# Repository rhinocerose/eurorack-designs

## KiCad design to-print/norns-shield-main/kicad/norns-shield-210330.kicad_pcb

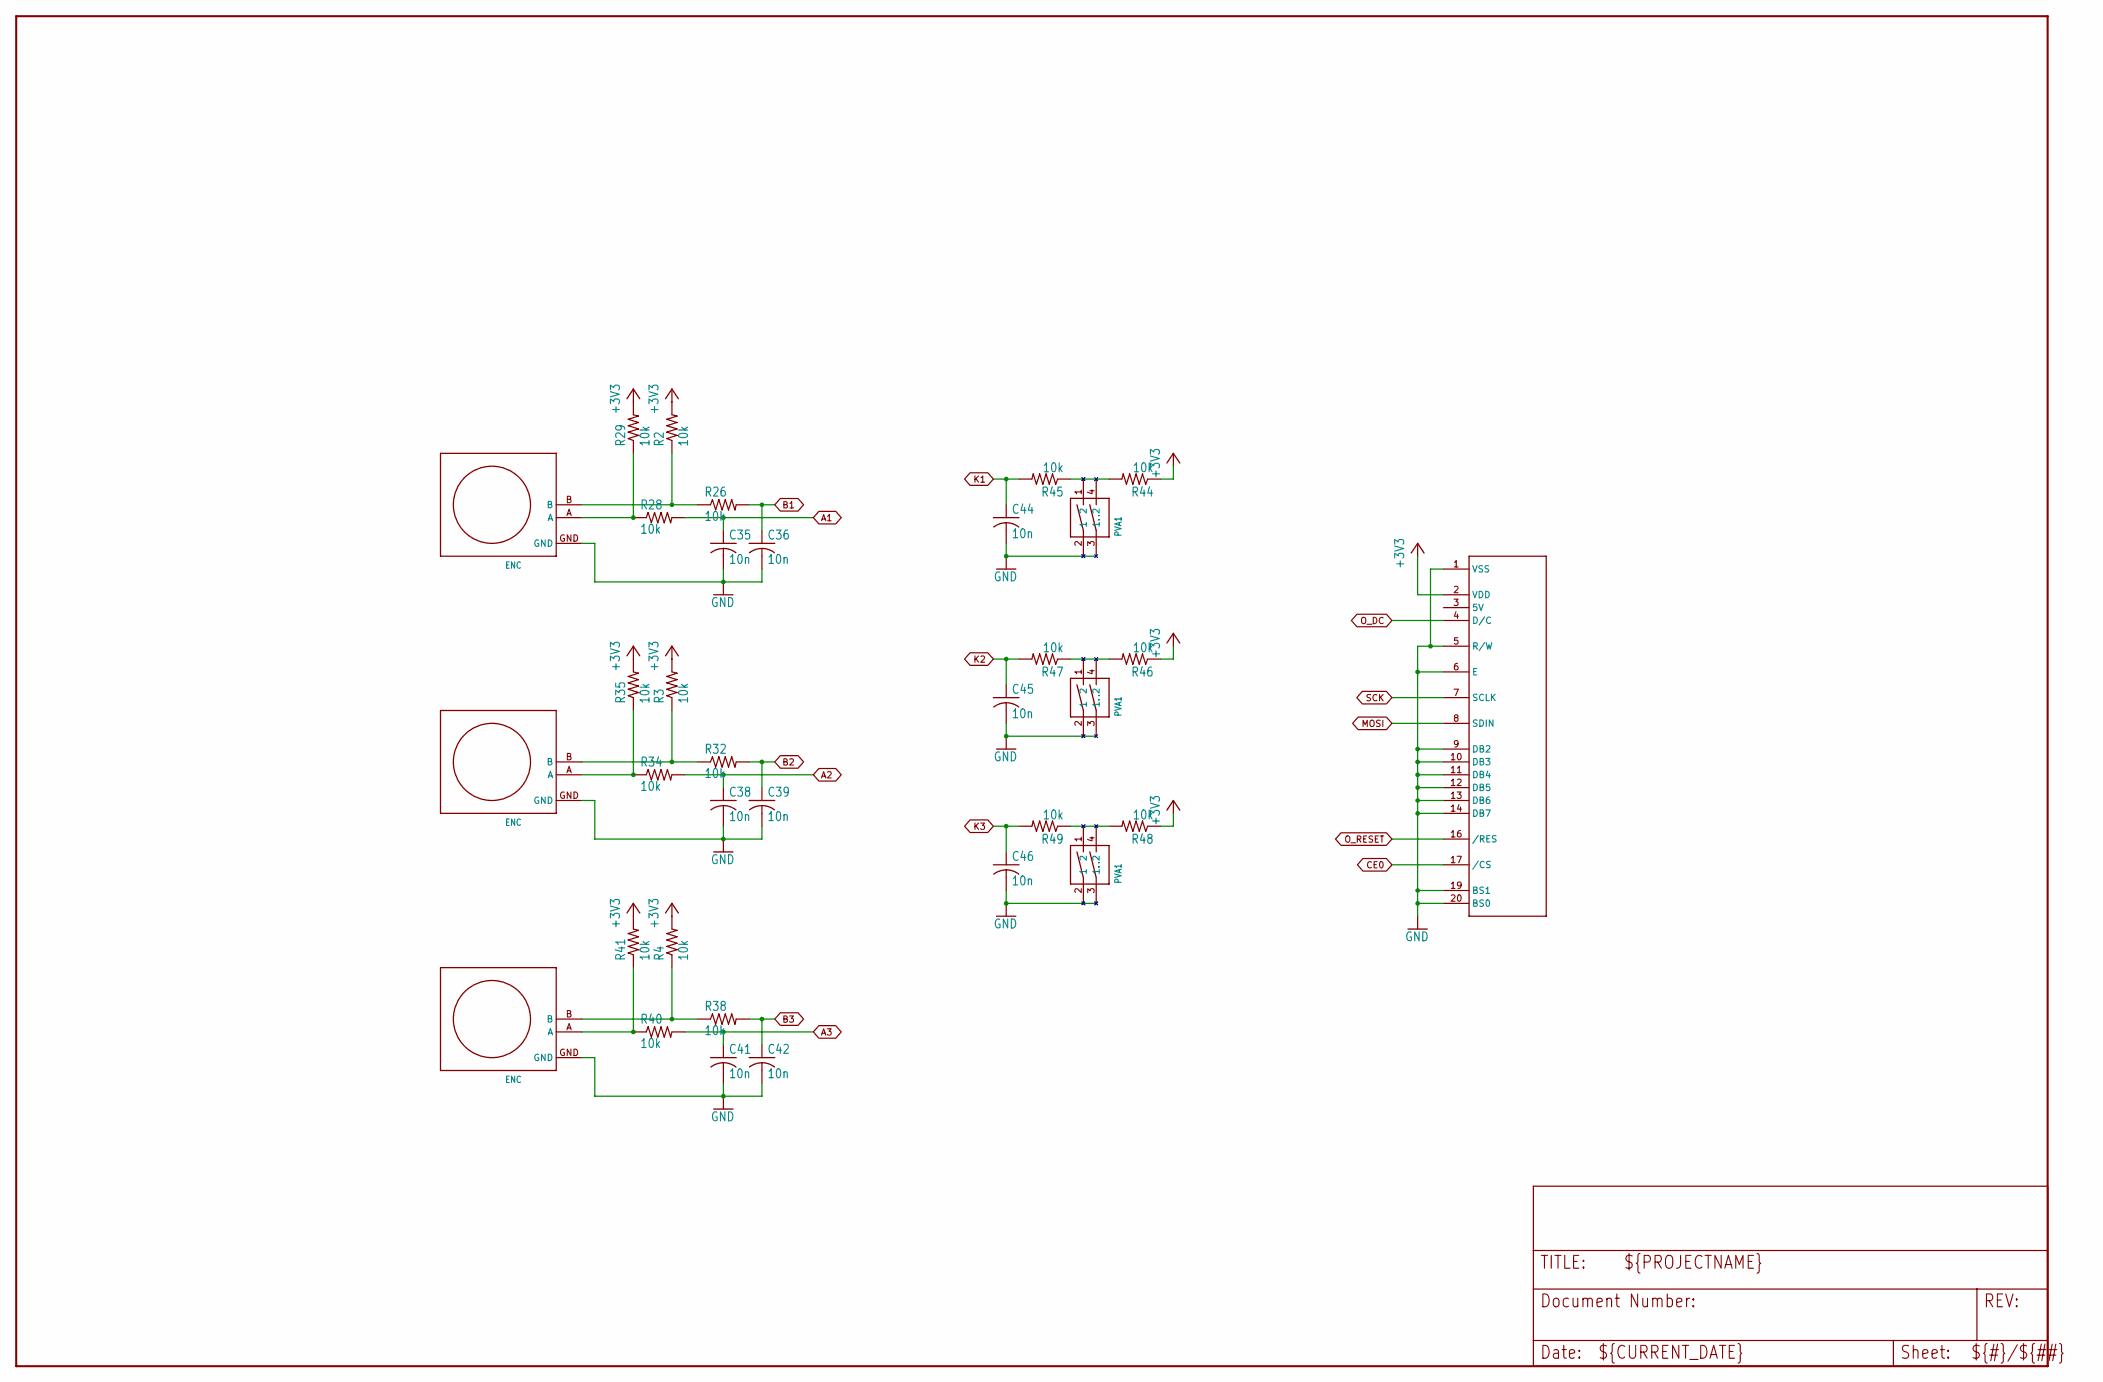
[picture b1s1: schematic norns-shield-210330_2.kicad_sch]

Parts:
C35, C36, C38, C39, C41, C42, C44, C45, C46: 10n; C0603
E1, E2, E3: ENC; PEC11RN
R2, R3, R4, R26, R28, R29, R32, R34, R35, R38, R40, R41, R44, R45, R46, R47, R48, R49: 10k; R0603
SW1, SW2, SW3: PVA1
U$1: OLED128X64; OLED-ALEPH

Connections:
+3V3: R2.2, R3.2, R4.2, R29.2, R35.2, R41.2, R44.1, R46.1, R48.1, U$1.2 (VDD); also elsewhere on the board
A1: C35.1, R28.2; also elsewhere on the board
A2: C38.1, R34.2; also elsewhere on the board
A3: C41.1, R40.2; also elsewhere on the board
B1: C36.1, R26.2; also elsewhere on the board
B2: C39.1, R32.2; also elsewhere on the board
B3: C42.1, R38.2; also elsewhere on the board
CE0: U$1.17 (/CS); also elsewhere on the board
GND: C35.2, C36.2, C38.2, C39.2, C41.2, C42.2, C44.2, C45.2, C46.2, E1.GND, E2.GND, E3.GND, SW1.2 (1), SW1.3 (1.), SW2.2 (1), SW2.3 (1.), SW3.2 (1), SW3.3 (1.), U$1.1 (VSS), U$1.5 (R/W), U$1.6 (E), U$1.9 (DB2), U$1.10 (DB3), U$1.11 (DB4), U$1.12 (DB5), U$1.13 (DB6), U$1.14 (DB7), U$1.19 (BS1), U$1.20 (BS0); also elsewhere on the board
K1: C44.1, R45.2; also elsewhere on the board
K2: C45.1, R47.2; also elsewhere on the board
K3: C46.1, R49.2; also elsewhere on the board
MOSI: U$1.8 (SDIN); also elsewhere on the board
unnamed: E1.A, R28.1, R29.1
unnamed: E1.B, R2.1, R26.1
unnamed: E2.B, R3.1, R32.1
unnamed: E2.A, R34.1, R35.1
unnamed: E3.B, R4.1, R38.1
unnamed: E3.A, R40.1, R41.1
O_DC: U$1.4 (D/C); also elsewhere on the board
O_RESET: U$1.16 (/RES); also elsewhere on the board
SCK: U$1.7 (SCLK); also elsewhere on the board

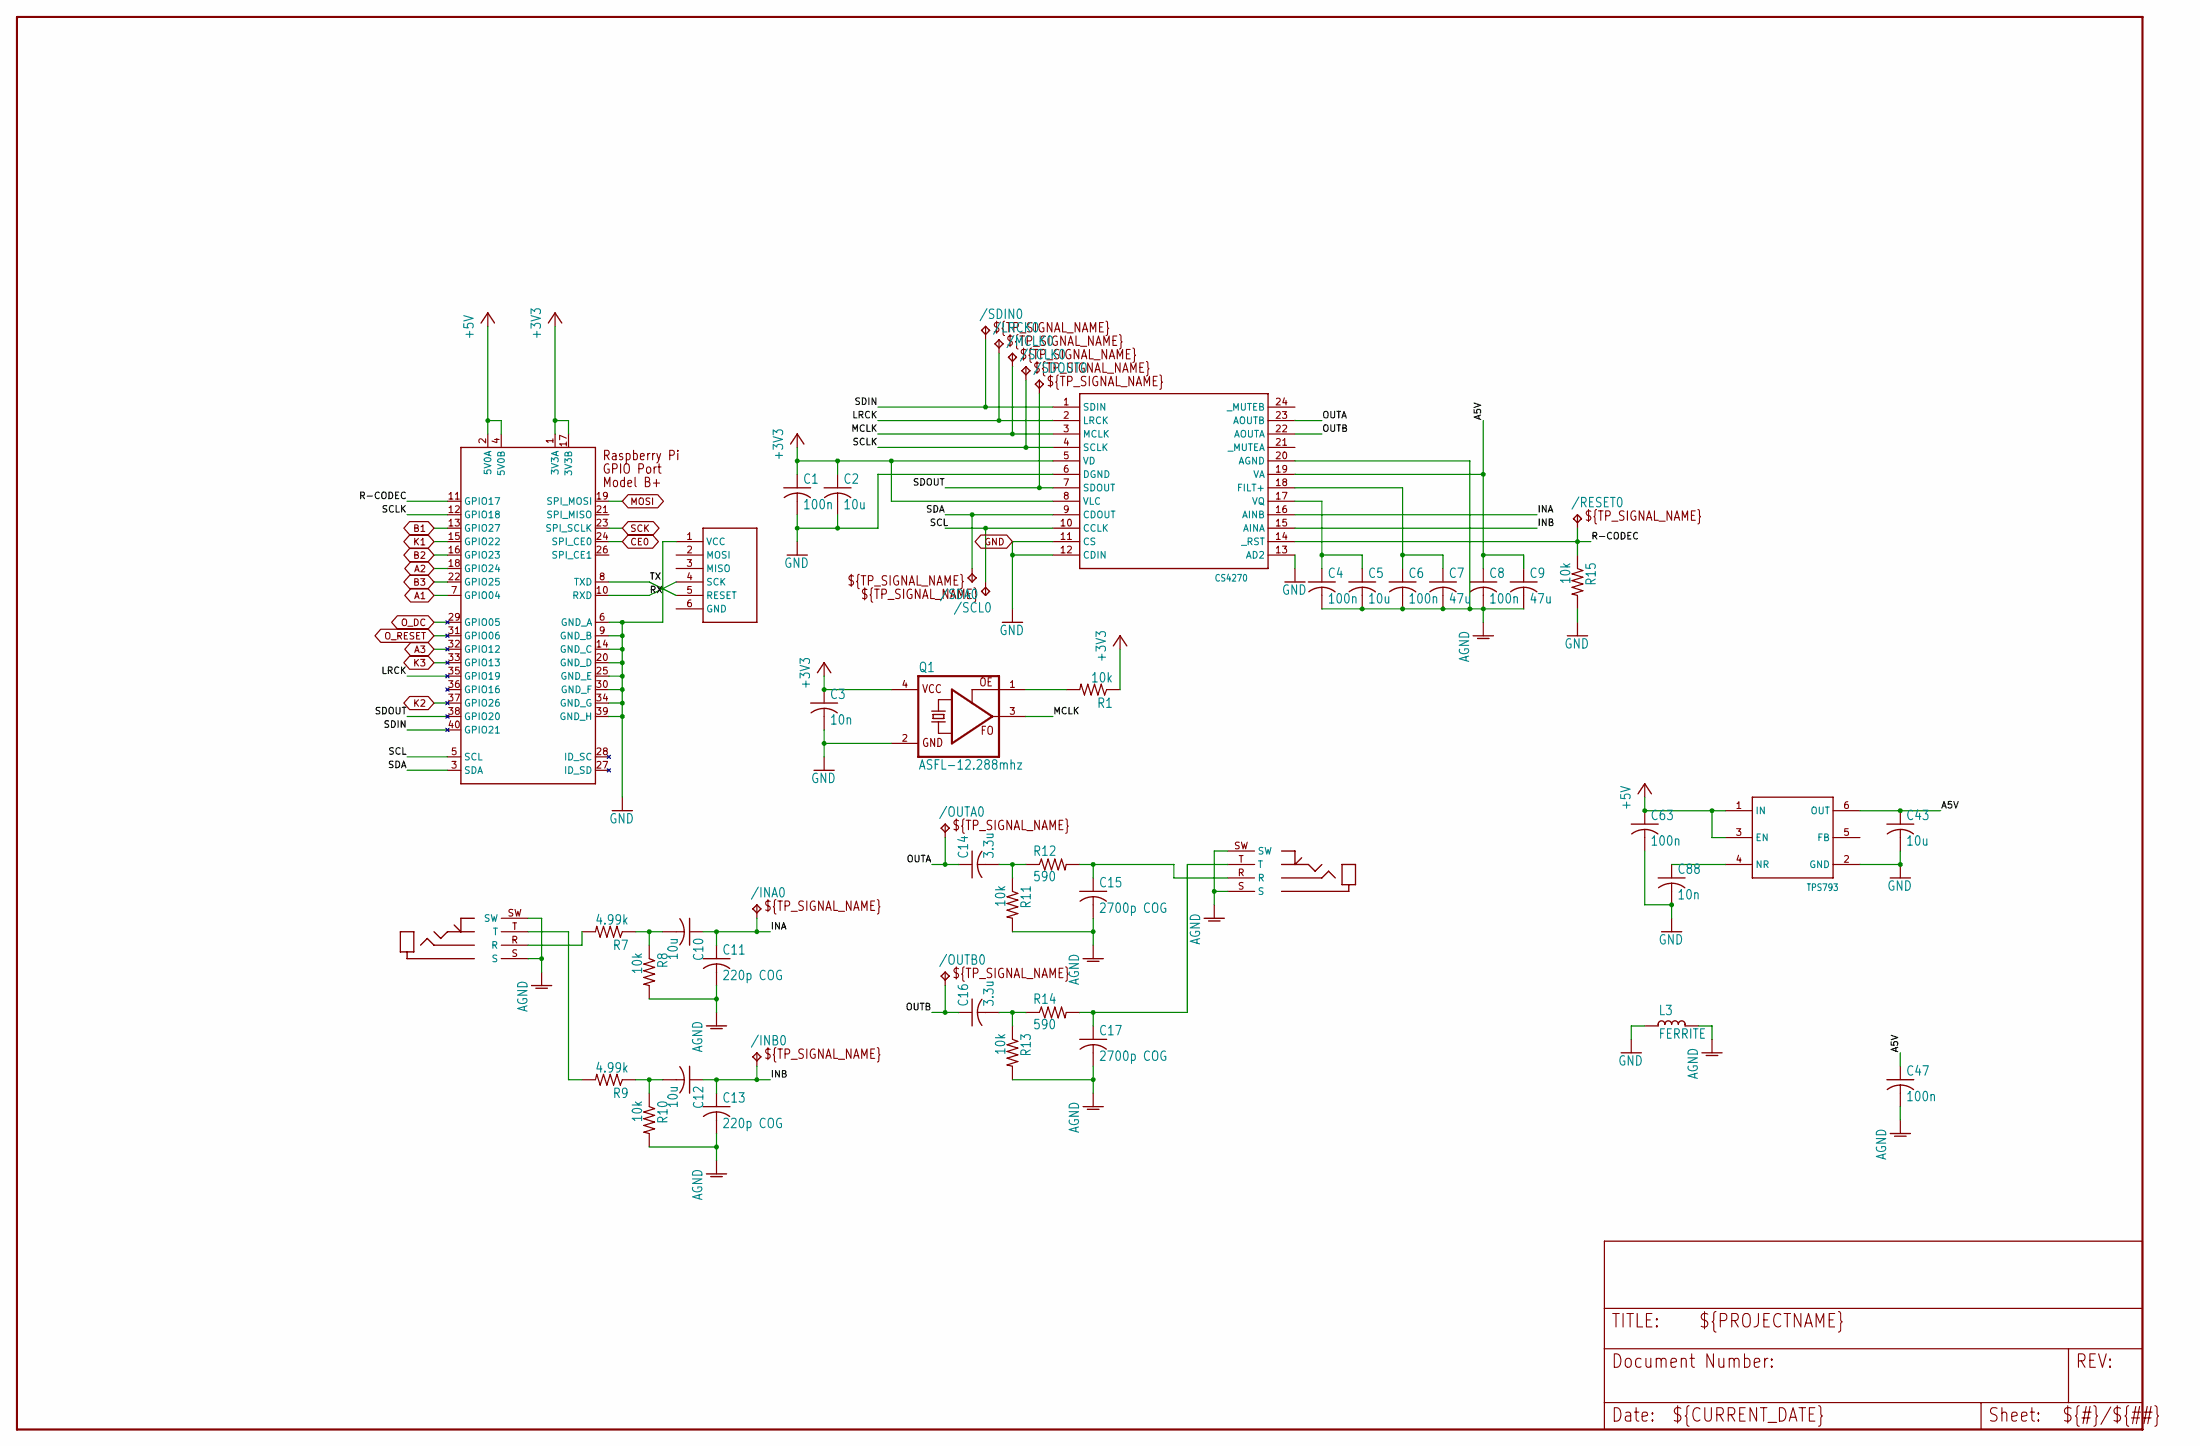
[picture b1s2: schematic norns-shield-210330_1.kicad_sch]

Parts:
/INA0: TPTP12R; TP12R
/INB0: TPTP12R; TP12R
/LRCK0: TPTP12R; TP12R
/MCLK0: TPTP12R; TP12R
/OUTA0: TPTP12R; TP12R
/OUTB0: TPTP12R; TP12R
/RESET0: TPTP12R; TP12R
/SCL0: TPTP12R; TP12R
/SCLK0: TPTP12R; TP12R
/SDA0: TPTP12R; TP12R
/SDIN0: TPTP12R; TP12R
/SDOUT0: TPTP12R; TP12R
C1, C4, C6, C8, C47, C63: 100n; C0603
C2, C5, C10, C12, C43: 10u; C0805
C3, C88: 10n; C0603
C7, C9: 47u; C1206
C11, C13: 220p COG; C0603
C14, C16: 3.3u; C0805
C15, C17: 2700p COG; C0603
J3: ISP-ROW
J-IN0: JACK-TRS-SW; JACK4832.2330
J-OUT0: JACK-TRS-SW; JACK4832.2330
L3: FERRITE; L0805
Q1: ASFL-12.288mhz; ASF
R1, R8, R10, R11, R13, R15: 10k; R0603
R7, R9: 4.99k; R0603
R12, R14: 590; R0603
U1: CS4270; TSSOP24
U11: TPS793; SSOP6
X1: RASPI_BOARD_B+#_E3; RASPI_BOARD_B+_EDGES_3DRILL

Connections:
+3V3: C1.1, C2.1, C3.1, Q1.4 (VCC), R1.1, U1.5 (VD), U1.8 (VLC), X1.1 (3V3A), X1.17 (3V3B); also elsewhere on the board
+5V: C63.1, U11.1 (IN), U11.3 (EN), X1.2 (5V0A), X1.4 (5V0B)
A1: X1.7 (GPIO04); also elsewhere on the board
A2: X1.18 (GPIO24); also elsewhere on the board
A3: X1.32 (GPIO12); also elsewhere on the board
A5V: C8.1, C9.1, C43.1, C47.1, U1.19 (VA), U11.6 (OUT)
AGND: C4.2, C5.2, C6.2, C7.2, C8.2, C9.2, C11.2, C13.2, C15.2, C17.2, C47.2, J-IN0.S, J-IN0.SW, J-OUT0.S, J-OUT0.SW, L3.1, R8.2, R10.2, R11.2, R13.2, U1.20 (AGND)
B1: X1.13 (GPIO27); also elsewhere on the board
B2: X1.16 (GPIO23); also elsewhere on the board
B3: X1.22 (GPIO25); also elsewhere on the board
CE0: X1.24 (SPI_CE0); also elsewhere on the board
GND: C1.2, C2.2, C3.2, C43.2, C63.2, C88.2, J3.1 (VCC), L3.2, Q1.2 (GND), R15.2, U1.6 (DGND), U1.11 (CS), U1.12 (CDIN), U1.13 (AD2), U11.2 (GND), X1.6 (GND_A), X1.9 (GND_B), X1.14 (GND_C), X1.20 (GND_D), X1.25 (GND_E), X1.30 (GND_F), X1.34 (GND_G), X1.39 (GND_H); also elsewhere on the board
INA: /INA0.TP, C10.1, C11.1, U1.16 (AINB)
INB: /INB0.TP, C12.1, C13.1, U1.15 (AINA)
K1: X1.15 (GPIO22); also elsewhere on the board
K2: X1.37 (GPIO26); also elsewhere on the board
K3: X1.33 (GPIO13); also elsewhere on the board
LRCK: /LRCK0.TP, U1.2 (LRCK), X1.35 (GPIO19)
MCLK: /MCLK0.TP, Q1.3 (FO), U1.3 (MCLK)
MOSI: X1.19 (SPI_MOSI); also elsewhere on the board
unnamed: Q1.1 (OE), R1.2
unnamed: C4.1, C5.1, U1.17 (VQ)
unnamed: C6.1, C7.1, U1.18 (FILT+)
unnamed: J-IN0.R, R7.2
unnamed: C10.2, R7.1, R8.1
unnamed: C12.2, R9.1, R10.1
unnamed: J-IN0.T, R9.2
unnamed: C16.2, R13.1, R14.1
unnamed: C14.2, R11.1, R12.1
unnamed: C15.1, J-OUT0.R, R12.2
unnamed: C17.1, J-OUT0.T, R14.2
unnamed: C88.1, U11.4 (NR)
OUTA: /OUTA0.TP, C14.1, U1.23 (AOUTB)
OUTB: /OUTB0.TP, C16.1, U1.22 (AOUTA)
O_DC: X1.29 (GPIO05); also elsewhere on the board
O_RESET: X1.31 (GPIO06); also elsewhere on the board
R-CODEC: /RESET0.TP, R15.1, U1.14 (_RST), X1.11 (GPIO17)
RX: J3.4 (SCK), X1.10 (RXD)
SCK: X1.23 (SPI_SCLK); also elsewhere on the board
SCL: /SCL0.TP, U1.10 (CCLK), X1.5 (SCL)
SCLK: /SCLK0.TP, U1.4 (SCLK), X1.12 (GPIO18)
SDA: /SDA0.TP, U1.9 (CDOUT), X1.3 (SDA)
SDIN: /SDIN0.TP, U1.1 (SDIN), X1.40 (GPIO21)
SDOUT: /SDOUT0.TP, U1.7 (SDOUT), X1.38 (GPIO20)
TX: J3.5 (RESET), X1.8 (TXD)

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
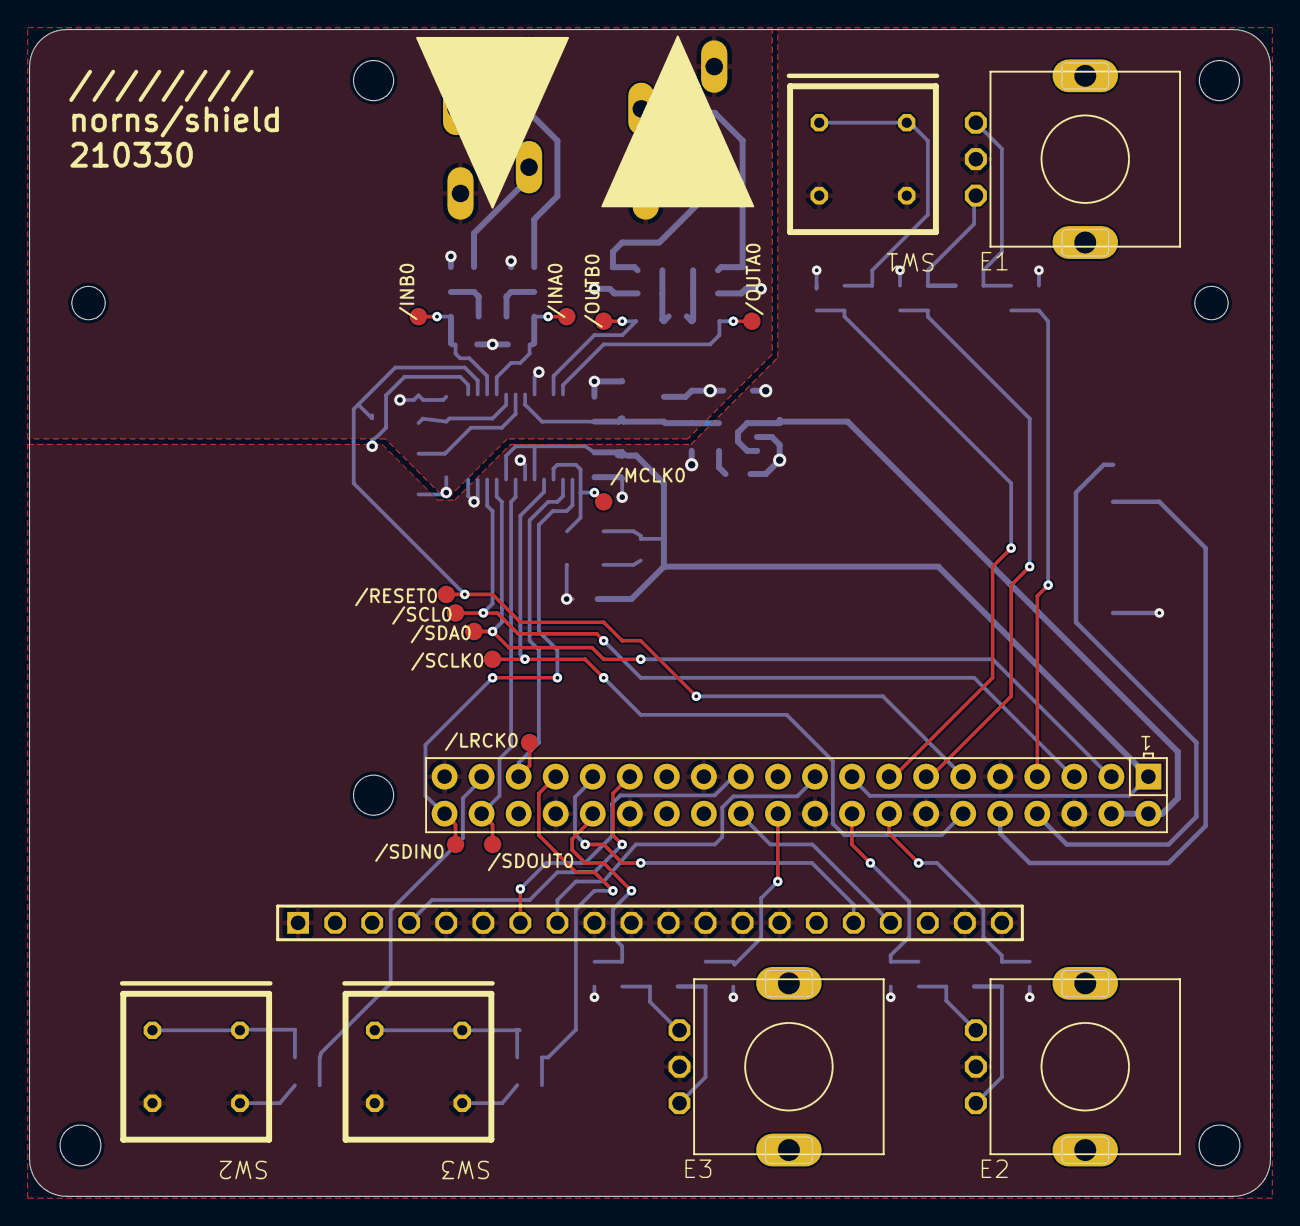
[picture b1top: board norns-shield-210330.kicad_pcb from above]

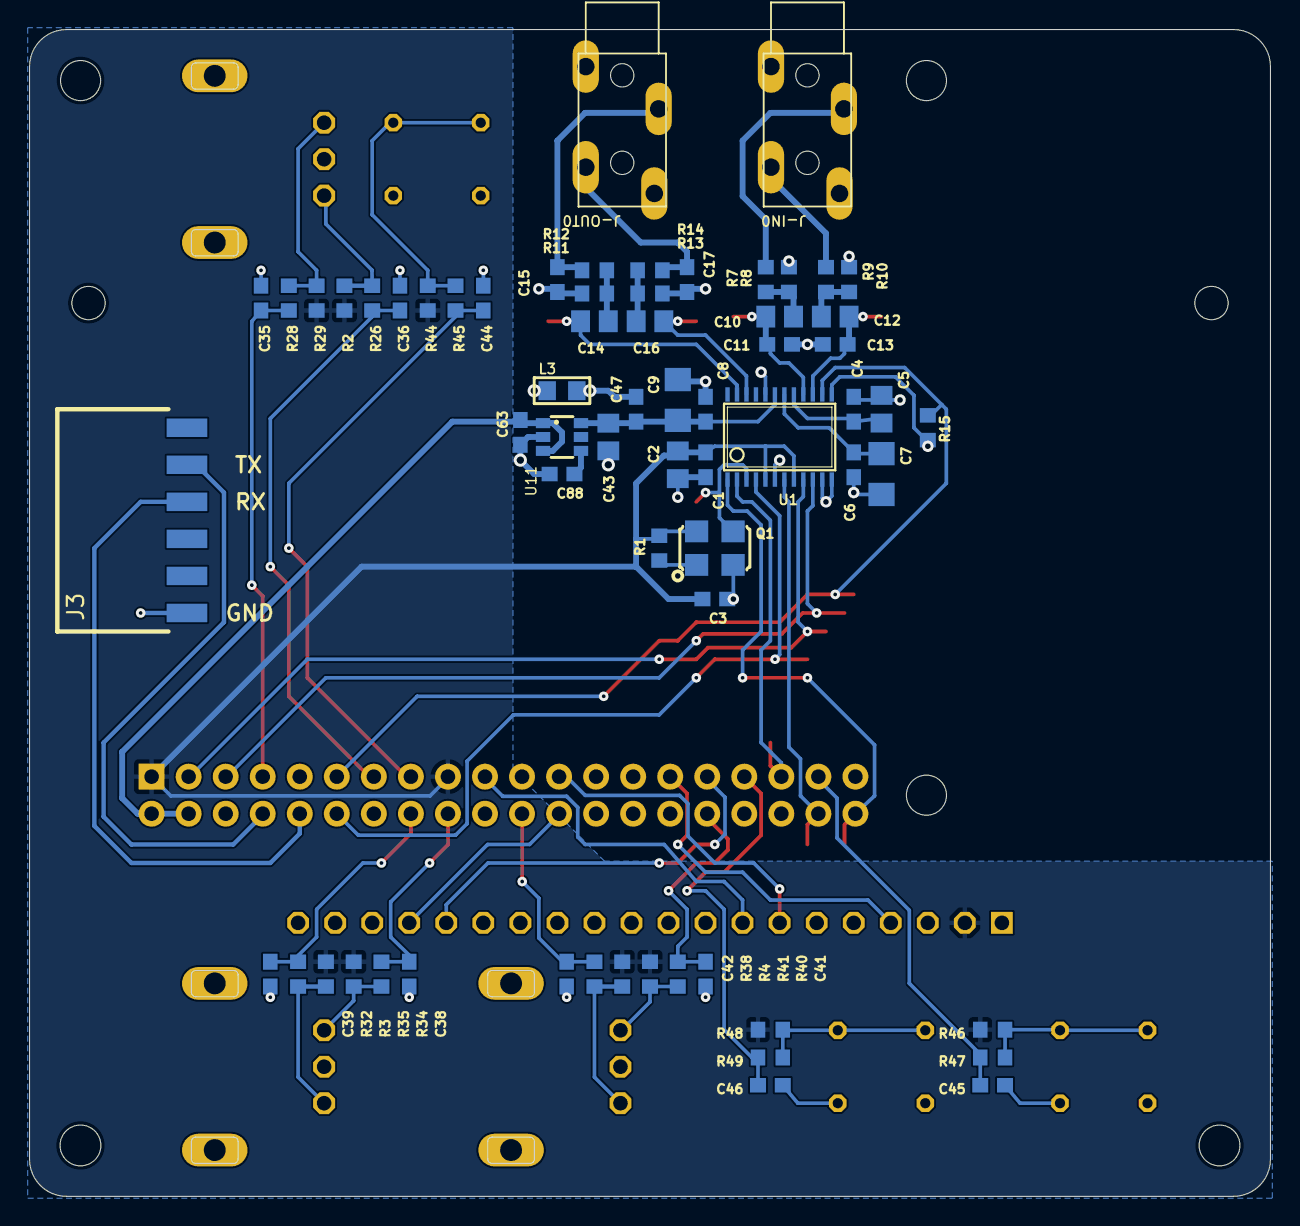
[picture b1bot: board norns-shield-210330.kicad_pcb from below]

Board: 2 copper layers, 85.1 x 80.0 mm, 87 parts (65 on the bottom side), 54 nets.

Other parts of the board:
@HOLE0, @HOLE1: (no value)

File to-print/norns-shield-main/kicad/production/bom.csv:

Designator,Footprint,Quantity,Value,LCSC Part #
"/INA0, /INB0, /LRCK0, /MCLK0, /OUTA0, /OUTB0, /RESET0, /SCL0, /SCLK0, /SDA0, /SDIN0, /SDOUT0",TP12R,12,TPTP12R,
"@HOLE0, @HOLE1",,2,,
"C1, C4, C47, C6, C63, C8",C0603,6,100n,
"C10, C12, C2, C43, C5",C0805,5,10u,
"C11, C13",C0603,2,220p COG,
"C14, C16",C0805,2,3.3u,
"C15, C17",C0603,2,2700p COG,
"C3, C35, C36, C38, C39, C41, C42, C44, C45, C46, C88",C0603,11,10n,
"C7, C9",C1206,2,47u,
"E1, E2, E3",PEC11RN,3,ENC,
"J-IN0, J-OUT0",JACK4832.2330,2,JACK-TRS-SW,
J3,ISP-ROW,1,ISP-ROW,
L3,L0805,1,FERRITE,
Q1,ASF,1,ASFL-12.288mhz,
"R1, R10, R11, R13, R15, R2, R26, R28, R29, R3, R32, R34, R35, R38, R4, R40, R41, R44, R45, R46, R47, R48, R49, R8",R0603,24,10k,
"R12, R14",R0603,2,590,
"R7, R9",R0603,2,4.99k,
"SW1, SW2, SW3",PVA1,3,PVA1,
U$1,OLED-ALEPH,1,OLED128X64,
U1,TSSOP24,1,CS4270,
U11,SSOP6,1,TPS793,
X1,RASPI_BOARD_B+_EDGES_3DRILL,1,RASPI_BOARD_B+#_E3,

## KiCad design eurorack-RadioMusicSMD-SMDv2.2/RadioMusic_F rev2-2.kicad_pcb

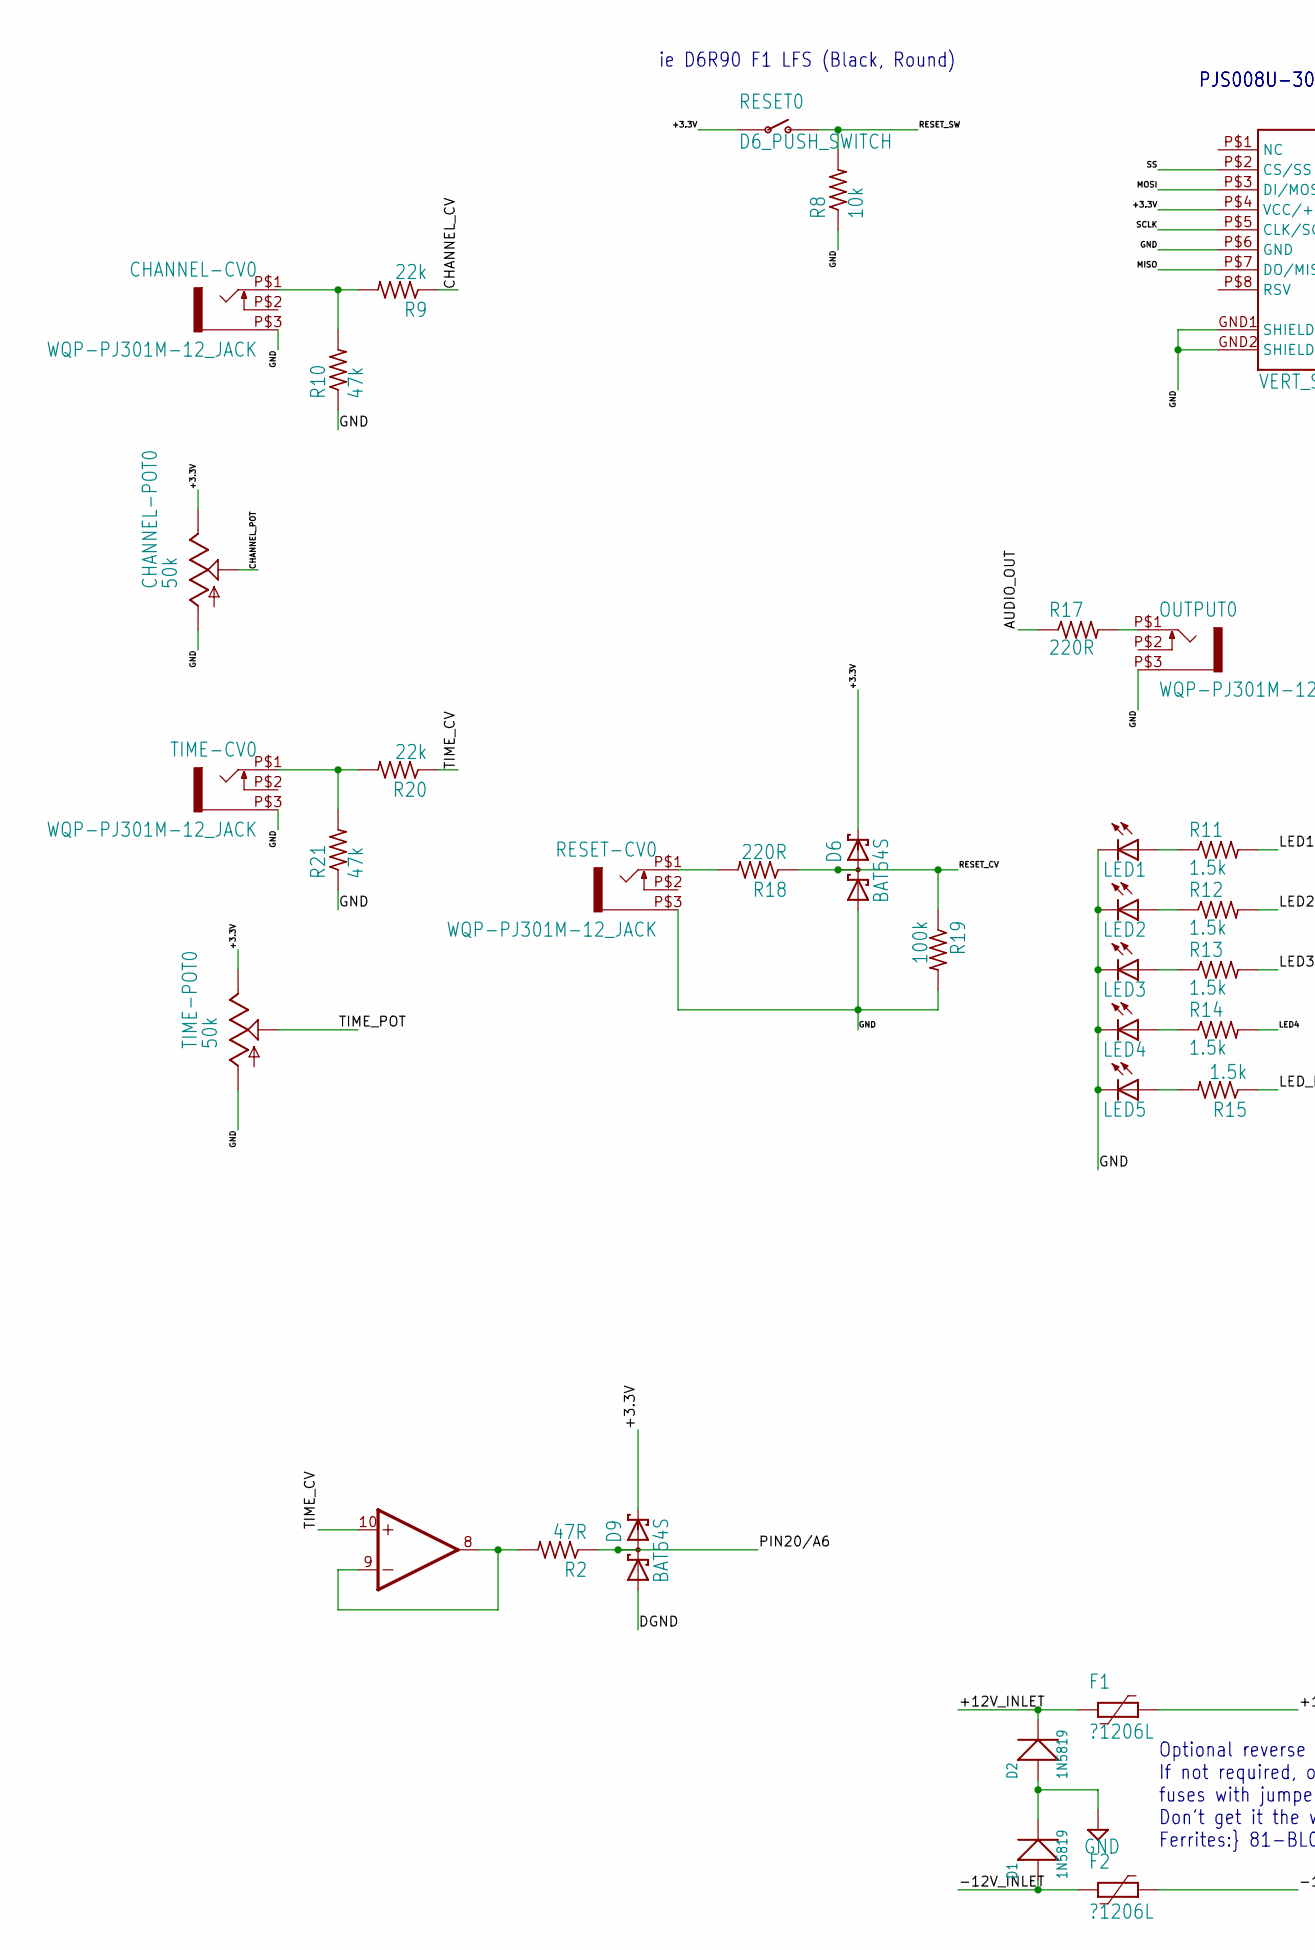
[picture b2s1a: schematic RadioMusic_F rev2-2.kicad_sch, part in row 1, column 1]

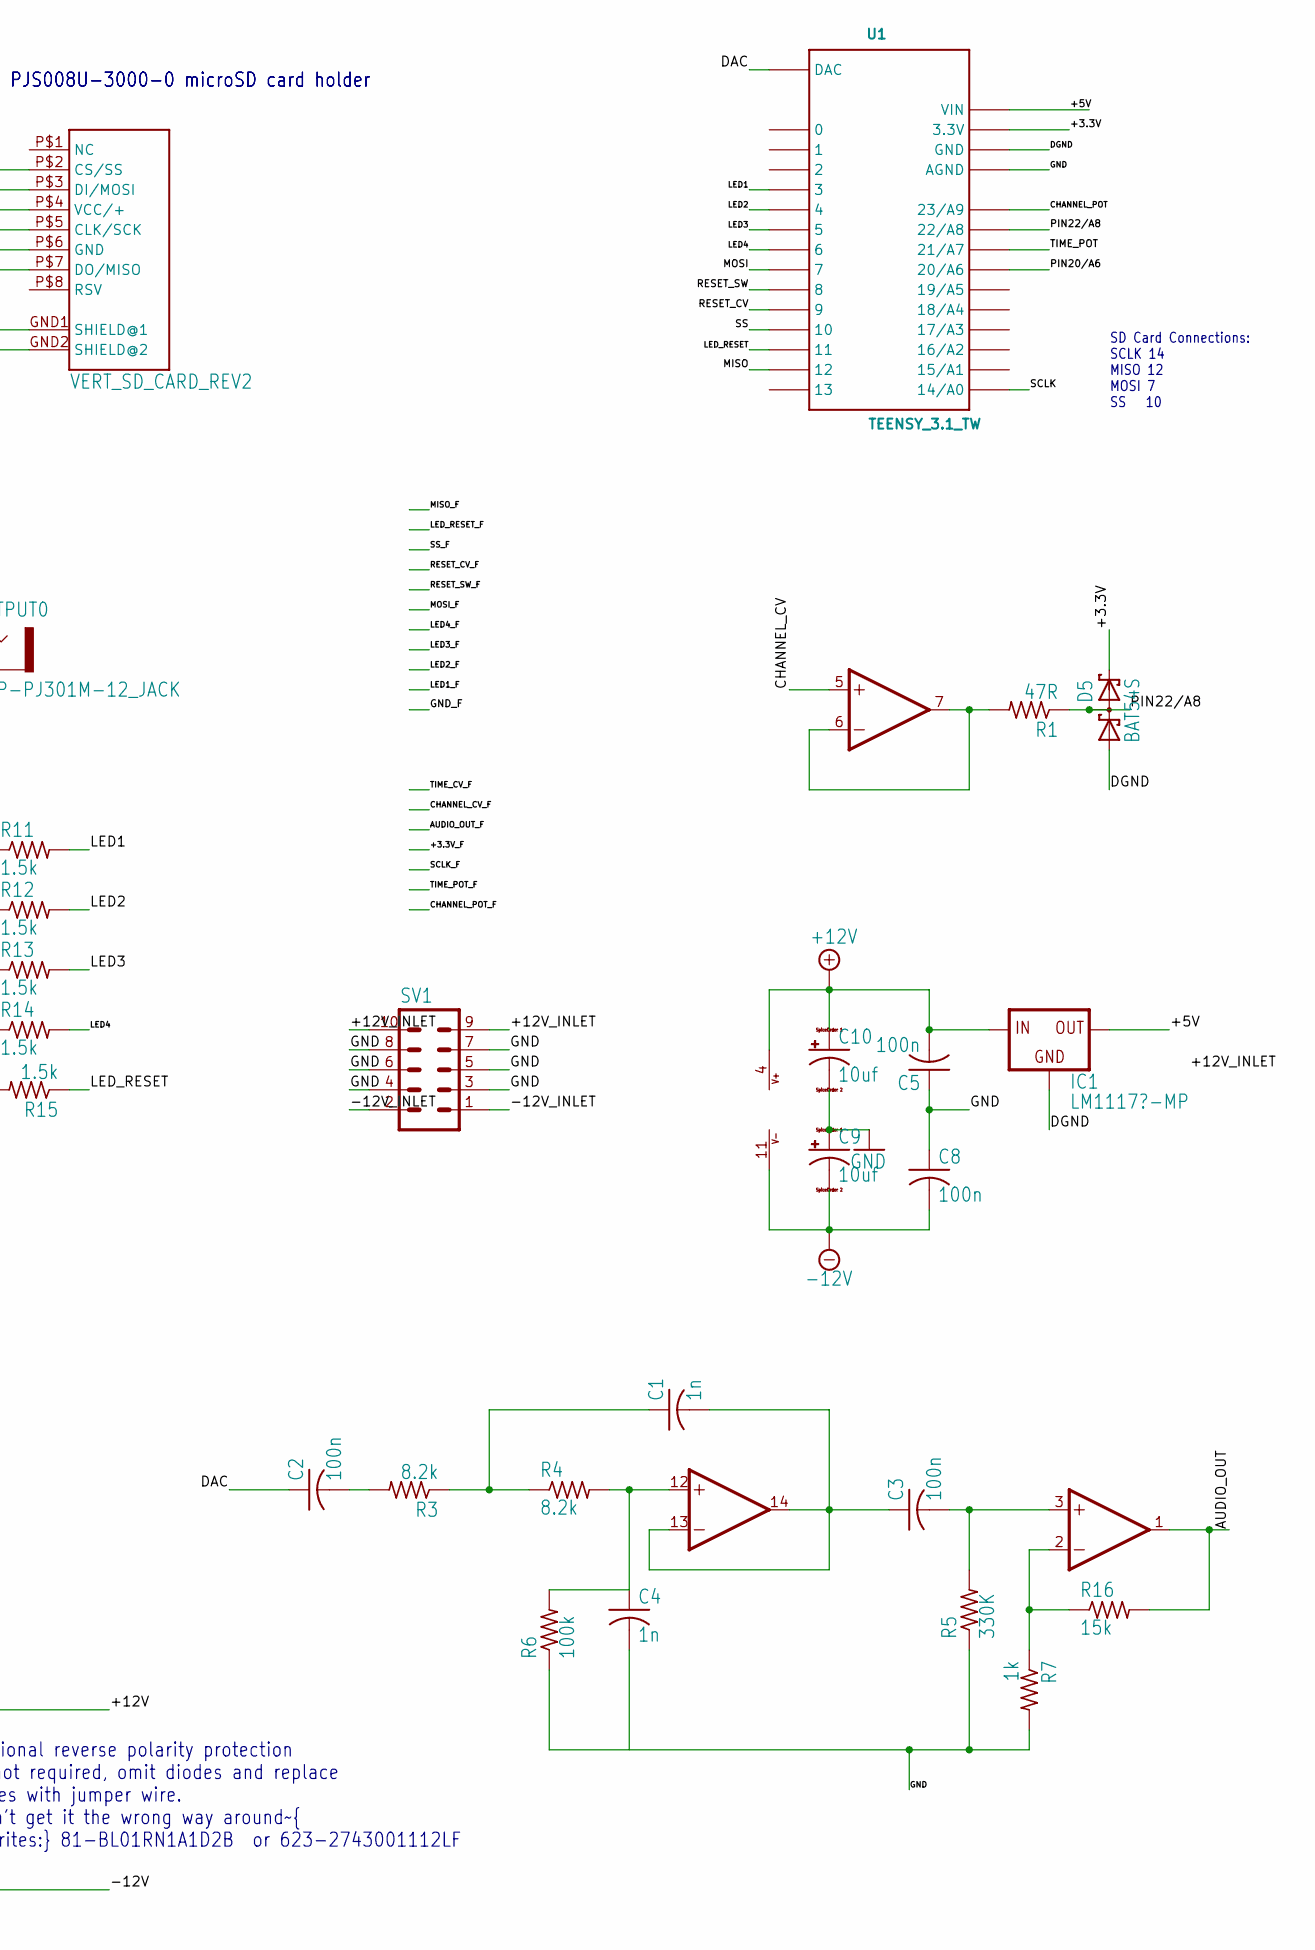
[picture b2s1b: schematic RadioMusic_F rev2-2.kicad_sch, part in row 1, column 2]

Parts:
C1, C4: 1n; C0805
C2, C3, C5, C8: 100n; C0805
C9, C10: 10uf; PANASONIC_B
CHANNEL-CV0: WQP-PJ301M-12_JACK
CHANNEL-POT0: 50k; EVUF
D1, D2: 1N5819; SOD-123
D5, D6, D9: BAT54S; SOT23
F1, F2: ?1206L; 1206L
IC1: LM1117?-MP; SOT223
IC4: TL074; SO14
LED1, LED2, LED3, LED4, LED5: LED3MM
OUTPUT0: WQP-PJ301M-12_JACK
R1, R2: 47R; R0805
R3, R4: 8.2k; R0805
R5: 330K; R0805
R6, R19: 100k; R0805
R7: 1k; R0805
R8: 10k; R0805
R9, R20: 22k; R0805
R10, R21: 47k; R0805
R11, R12, R13, R14, R15: 1.5k; R0805
R16: 15k; R0805
R17, R18: 220R; R0805
RESET0: D6_PUSH_SWITCH; D6_BUTTON_RND
RESET-CV0: WQP-PJ301M-12_JACK
SV1: 10_PIN_HEADER; MA05-2
TIME-CV0: WQP-PJ301M-12_JACK
TIME-POT0: 50k; EVUF
U1: TEENSY_3.1_TW
X1: VERT_SD_CARD_REV2; VERT_MICROSD_REV2

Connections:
+3.3V: CHANNEL-POT0.3 (E), D5.2 (C2), D6.2 (C2), D9.2 (C2), RESET0.P$3, RESET0.P$4, TIME-POT0.3 (E), U1.3.3V, X1.P$4 (VCC/+)
+5V: IC1.2 (OUT), IC1.4 (OUT), U1.VIN
+12V: C5.2, C10.+, F1.1, IC1.3 (IN), IC4.4 (V+)
+12V_INLET: D2.-, F1.2, SV1.9, SV1.10
-12V: C8.2, C9.-, F2.1, IC4.11 (V-)
-12V_INLET: D1.+, F2.2, SV1.1, SV1.2
AUDIO_OUT: IC4.1 (OUT), R16.2, R17.1
CHANNEL_CV: IC4.5 (+IN), R9.1
CHANNEL_POT: CHANNEL-POT0.2 (S), U1.23/A9
DAC: C2.1, U1.DAC
DGND: D5.1 (A1), D9.1 (A1), IC1.1 (GND), U1.GND
GND: C4.2, C5.1, C8.1, C9.+, C10.-, CHANNEL-CV0.P$3 (1), CHANNEL-POT0.1 (A), D1.-, D2.+, D6.1 (A1), LED1.K (C), LED2.K (C), LED3.K (C), LED4.K (C), LED5.K (C), OUTPUT0.P$3 (1), R5.1, R6.1, R7.2, R8.1, R10.1, R19.2, R21.1, RESET-CV0.P$3 (1), SV1.3, SV1.4, SV1.5, SV1.6, SV1.7, SV1.8, TIME-CV0.P$3 (1), TIME-POT0.1 (A), U1.AGND, X1.GND1 (SHIELD@1), X1.GND2 (SHIELD@2), X1.P$6 (GND)
LED1: R11.2, U1.3
LED2: R12.2, U1.4
LED3: R13.2, U1.5
LED4: R14.2, U1.6
LED_RESET: R15.1, U1.11
MISO: U1.12, X1.P$7 (DO/MISO)
MOSI: U1.7, X1.P$3 (DI/MOSI)
unnamed: IC4.6 (-IN), IC4.7 (OUT), R1.2
unnamed: C4.1, IC4.12 (+IN), R4.2, R6.2
unnamed: OUTPUT0.P$1 (2), R17.2
unnamed: C1.1, R3.1, R4.1
unnamed: C1.2, C3.1, IC4.13 (-IN), IC4.14 (OUT)
unnamed: C3.2, IC4.3 (+IN), R5.2
unnamed: IC4.2 (-IN), R7.1, R16.1
unnamed: IC4.8 (OUT), IC4.9 (-IN), R2.2
unnamed: CHANNEL-CV0.P$1 (2), R9.2, R10.2
unnamed: C2.2, R3.2
unnamed: LED2.A, R12.1
unnamed: LED4.A, R14.1
unnamed: LED3.A, R13.1
unnamed: R18.2, RESET-CV0.P$1 (2)
unnamed: LED1.A, R11.1
unnamed: LED5.A, R15.2
PIN20/A6: D9.3 (C1A2), R2.1, U1.20/A6
PIN22/A8: D5.3 (C1A2), R1.1, U1.22/A8
RESET_CV: D6.3 (C1A2), R18.1, R19.1, U1.9
RESET_SW: R8.2, RESET0.P$1 (O), RESET0.P$2 (O), U1.8
SCLK: U1.14/A0, X1.P$5 (CLK/SCK)
SS: U1.10, X1.P$2 (CS/SS)
TEMP: R20.2, R21.2, TIME-CV0.P$1 (2)
TIME_CV: IC4.10 (+IN), R20.1
TIME_POT: TIME-POT0.2 (S), U1.21/A7

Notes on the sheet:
ie D6R90 F1 LFS (Black, Round)
SD Card Connections: SCLK 14 MISO 12 MOSI 7 SS 10
PJS008U-3000-0 microSD card holder
Optional reverse polarity protection If not required, omit diodes and replace fuses with jumper wire. Don't get it the wrong way around~{ Ferrites:} 81-BL01RN1A1D2B or 623-2743001112LF

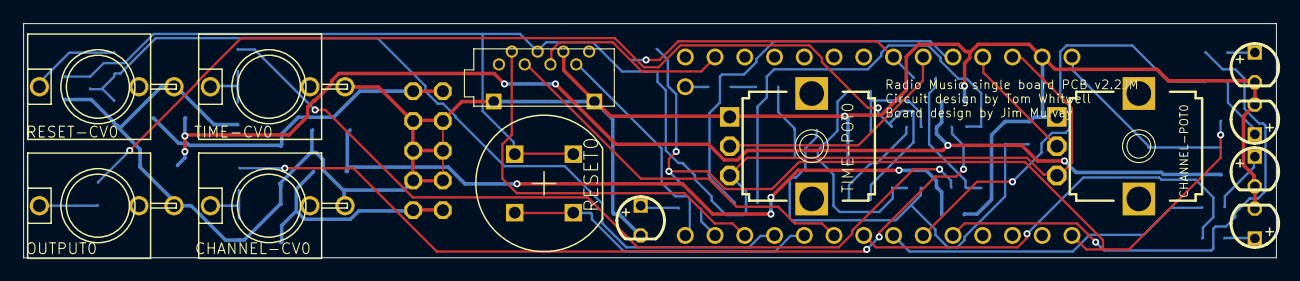
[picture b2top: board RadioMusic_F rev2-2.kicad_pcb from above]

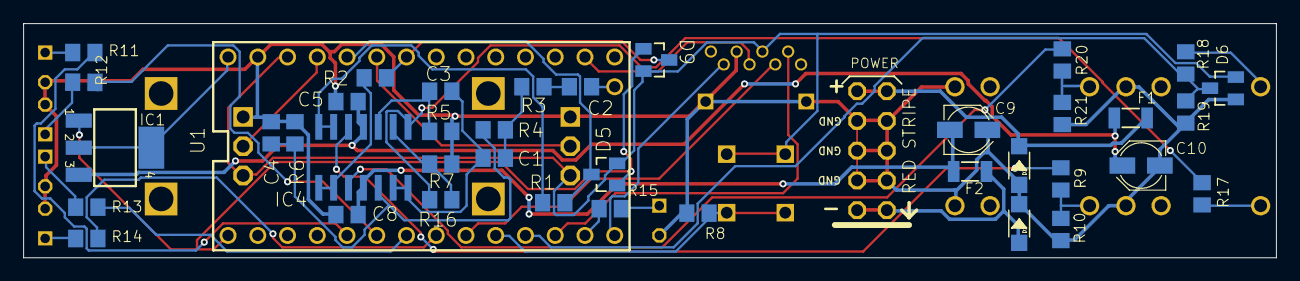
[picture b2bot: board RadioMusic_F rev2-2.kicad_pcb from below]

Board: 2 copper layers, 107.0 x 20.0 mm, 53 parts (40 on the bottom side), 44 nets.

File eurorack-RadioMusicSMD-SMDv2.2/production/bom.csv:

Designator,Footprint,Quantity,Value,LCSC Part #
"C1, C4",C0805_334,2,1n,
"C10, C9",PANASONIC_B_348,2,10uf,
"C2, C3, C5, C8",C0805_334,4,100n,
"CHANNEL-CV0, OUTPUT0, RESET-CV0, TIME-CV0",WQP-PJ301M-12_JACK,4,,
"CHANNEL-POT0, TIME-POT0",EVUF,2,50k,
"D1, D2",SOD-123_467,2,1N5819,
"D5, D6, D9",SOT23_210,3,BAT54S,
"F1, F2",1206L,2,1206L020,
IC1,SOT223,1,LM1117MP-5.0,
IC4,SO14_262,1,TL074,
"LED1, LED2, LED3, LED4, LED5",LED3MM,5,,
"R1, R2",R0805_334,2,47R,
"R10, R21",R0805_334,2,47k,
"R11, R12, R13, R14, R15",R0805_334,5,1.5k,
R16,R0805_334,1,15k,
"R17, R18",R0805_334,2,220R,
"R19, R6",R0805_334,2,100k,
"R20, R9",R0805_334,2,22k,
"R3, R4",R0805_334,2,8.2k,
R5,R0805_334,1,330K,
R7,R0805_334,1,1k,
R8,R0805_334,1,10k,
RESET0,D6_BUTTON_RND,1,D6_PUSH_SWITCH,
SV1,MA05-2,1,,
U1,TEENSY_3.1_TW,1,TEENSY_3.1_TW,
X1,VERT_MICROSD_REV2,1,VERT_SD_CARD_REV2,

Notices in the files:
1uO_c-mk2-master/kicad/1uO_c_v_2.2.kicad_pcb:
CC-BY-SA 4.0
sample-radio-music/RadioMusic_F.kicad_pcb:
February 2015 CC-BY-SA
